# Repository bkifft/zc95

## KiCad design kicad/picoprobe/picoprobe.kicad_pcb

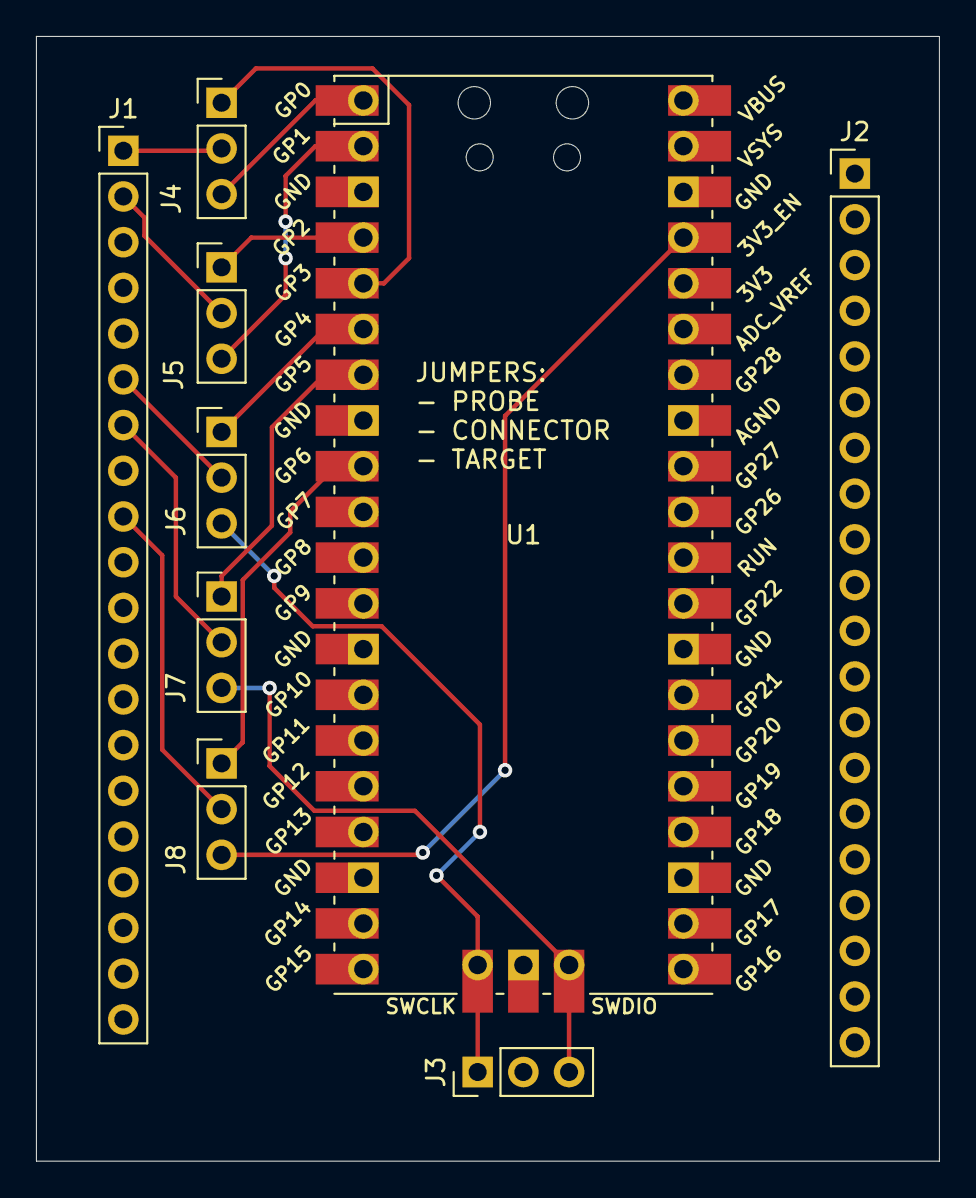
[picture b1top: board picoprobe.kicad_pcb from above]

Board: 2 copper layers, 50.2 x 62.5 mm, 9 parts (0 on the bottom side), 16 nets.

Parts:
J1: Connector left; PinHeader_1x20_P2.54mm_Vertical
J2: Connector right; PinHeader_1x20_P2.54mm_Vertical
J3: SWD; PinHeader_1x03_P2.54mm_Vertical
J4: UART 1; PinHeader_1x03_P2.54mm_Vertical
J5: UART 2; PinHeader_1x03_P2.54mm_Vertical
J6: SWCLK; PinHeader_1x03_P2.54mm_Vertical
J7: SWDIO; PinHeader_1x03_P2.54mm_Vertical
J8: RST; PinHeader_1x03_P2.54mm_Vertical
U1: Pico; RPi_Pico_SMD_TH

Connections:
GND: J1.3, J1.8, J1.13, J1.18, J2.3, J2.8, J2.13, J2.18, J3.2, U1.3, U1.8, U1.13, U1.18, U1.23, U1.28, U1.33, U1.38, U1.42
RST: J1.9, J8.2
SWCLK: J1.6, J6.2
SWDIO: J1.7, J7.2
UART1: J1.1, J4.2
UART2: J1.2, J5.2
pro_rst: J8.1, U1.9
pro_rx: J5.1, U1.4
pro_swclk: J6.1, U1.6
pro_swdio: J7.1, U1.7
pro_tx: J4.1, U1.5
tar_rst: J8.3, U1.37
tar_rx: J4.3, U1.1
tar_swclk: J3.1, J6.3, U1.41
tar_swdio: J3.3, J7.3, U1.43
tar_tx: J5.3, U1.2

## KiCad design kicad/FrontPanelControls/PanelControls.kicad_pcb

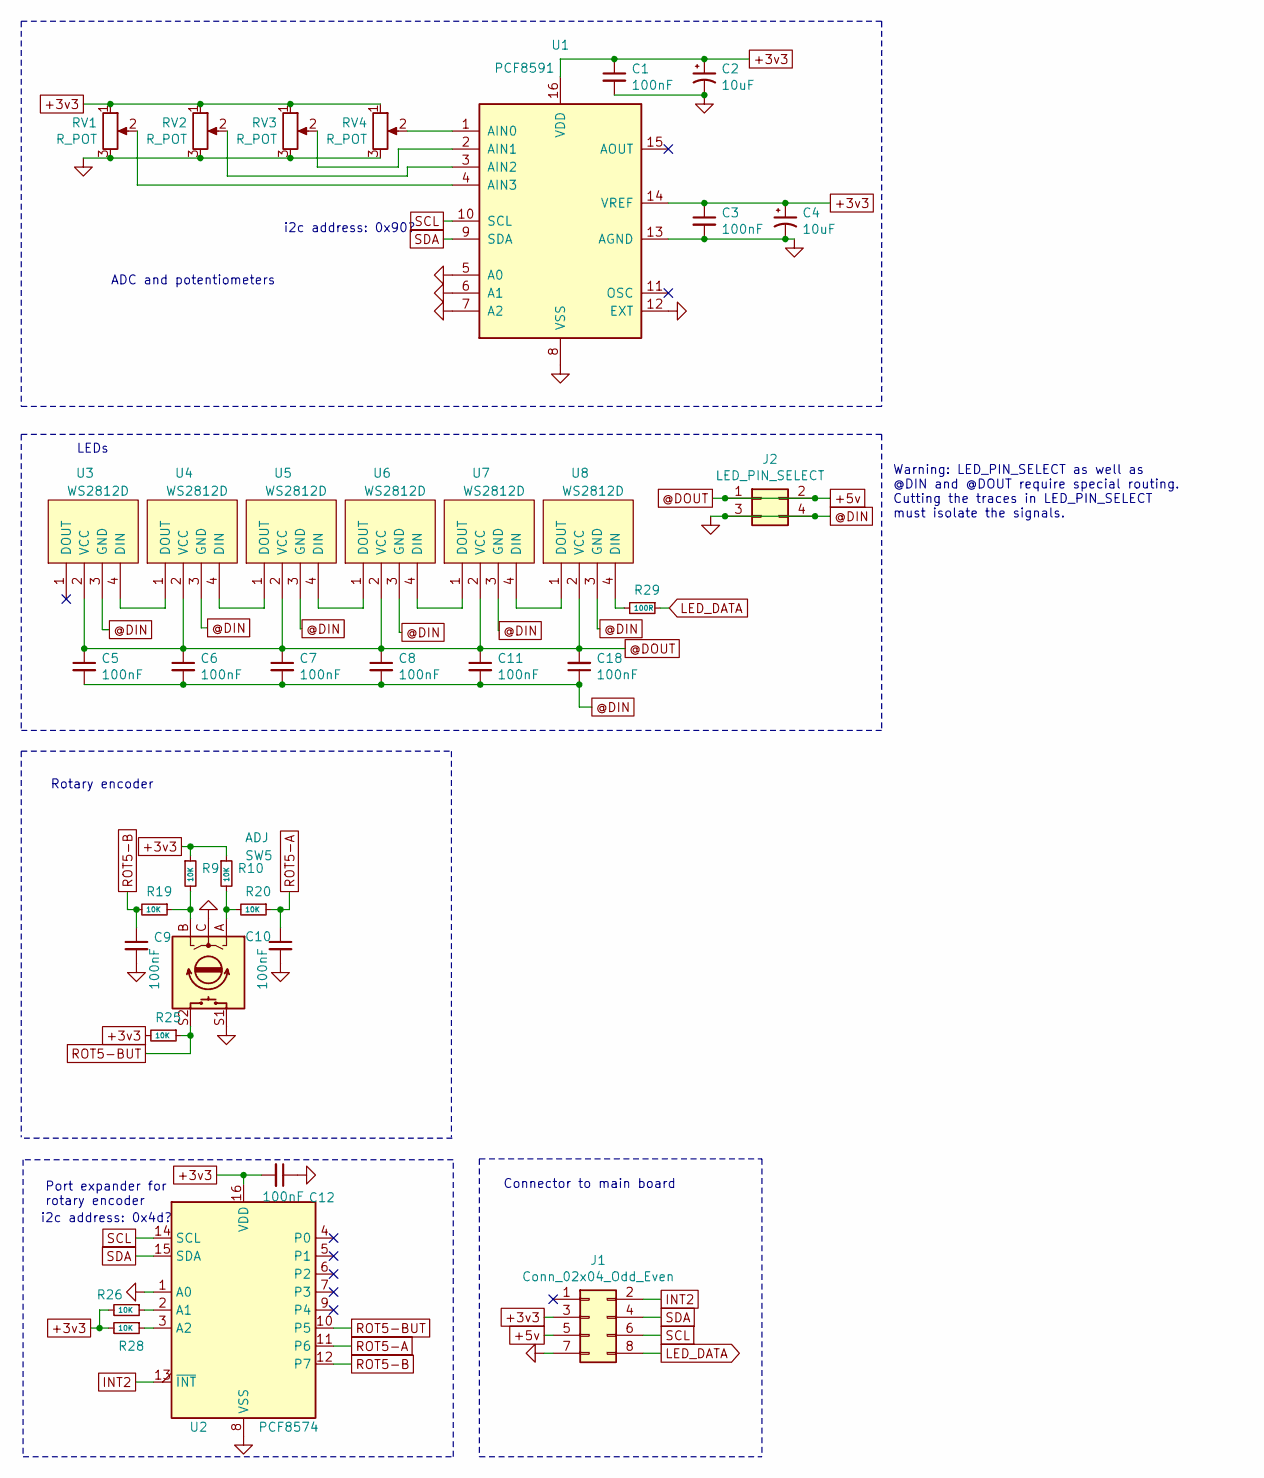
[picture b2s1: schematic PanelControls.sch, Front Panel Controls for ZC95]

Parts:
C1, C3, C5, C6, C7, C8, C9, C10, C11, C12, C18: 100nF; C_Disc_D3.0mm_W2.0mm_P2.50mm
C2, C4: 10uF; CP_Radial_D4.0mm_P2.00mm; LCSC C191532
J1: Conn_02x04_Odd_Even; IDC-Header_2x04_P2.54mm_Vertical
J2: LED_PIN_SELECT; PinHeader_2x02_P2.54mm_Vertical
R9, R10, R19, R20, R25, R26, R28: 10K; R_Axial_DIN0207_L6.3mm_D2.5mm_P7.62mm_Horizontal
R29: 100R; R_Axial_DIN0207_L6.3mm_D2.5mm_P7.62mm_Horizontal
RV1, RV2, RV3, RV4: R_POT; ALPSALPINE RK09L1140A2U
SW5: ADJ; BOURNS PEC11L-4125F-S0020
U1: PCF8591; SO-16_5.3x10.2mm_P1.27mm
U2: PCF8574; DIP-16_W7.62mm_LongPads
U3, U4, U5, U6, U7, U8: WS2812D; WS2812D-F5

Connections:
+3v3: C1.1, C2.1, C3.1, C4.1, C12.2, J1.3, R9.1, R10.1, R25.2, R26.2, R28.2, RV1.1, RV2.1, RV3.1, RV4.1, U1.14 (VREF), U1.16 (VDD), U2.16 (VDD)
+5v: C5.1, C6.1, C7.1, C8.1, C11.1, C18.2, J1.5, J2.1, J2.2, U3.2 (VCC), U4.2 (VCC), U5.2 (VCC), U6.2 (VCC), U7.2 (VCC), U8.2 (VCC)
@DIN: C1.2, C2.2, C3.2, C4.2, C5.2, C6.2, C7.2, C8.2, C9.2, C10.2, C11.2, C12.1, C18.1, J1.7, J2.3, J2.4, RV1.3, RV2.3, RV3.3, RV4.3, SW5.C, SW5.S1, U1.5 (A0), U1.6 (A1), U1.7 (A2), U1.8 (VSS), U1.12 (EXT), U1.13 (AGND), U2.1 (A0), U2.8 (VSS), U3.3 (GND), U4.3 (GND), U5.3 (GND), U6.3 (GND), U7.3 (GND), U8.3 (GND)
INT2: J1.2, U2.13 (~INT~)
LED_DATA: J1.8, R29.1
unnamed: R10.2, R20.2, SW5.A
unnamed: R9.2, R19.1, SW5.B
unnamed: R26.1, U2.2 (A1)
unnamed: R28.1, U2.3 (A2)
unnamed: R29.2, U8.4 (DIN)
unnamed: RV1.2, U1.4 (AIN3)
unnamed: RV2.2, U1.3 (AIN2)
unnamed: RV3.2, U1.2 (AIN1)
unnamed: RV4.2, U1.1 (AIN0)
unnamed: U3.4 (DIN), U4.1 (DOUT)
unnamed: U4.4 (DIN), U5.1 (DOUT)
unnamed: U5.4 (DIN), U6.1 (DOUT)
unnamed: U6.4 (DIN), U7.1 (DOUT)
unnamed: U7.4 (DIN), U8.1 (DOUT)
ROT5-A: C10.1, R20.1, U2.11 (P6)
ROT5-B: C9.1, R19.2, U2.12 (P7)
ROT5-BUT: R25.1, SW5.S2, U2.10 (P5)
SCL: J1.6, U1.10 (SCL), U2.14 (SCL)
SDA: J1.4, U1.9 (SDA), U2.15 (SDA)

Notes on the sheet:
LEDs
ADC and potentiometers
Port expander for rotary encoder
Rotary encoder
Connector to main board
i2c address: 0x90?
i2c address: 0x4d?
Warning: LED_PIN_SELECT as well as @DIN and @DOUT require special routing. Cutting the traces in LED_PIN_SELECT must isolate the signals.

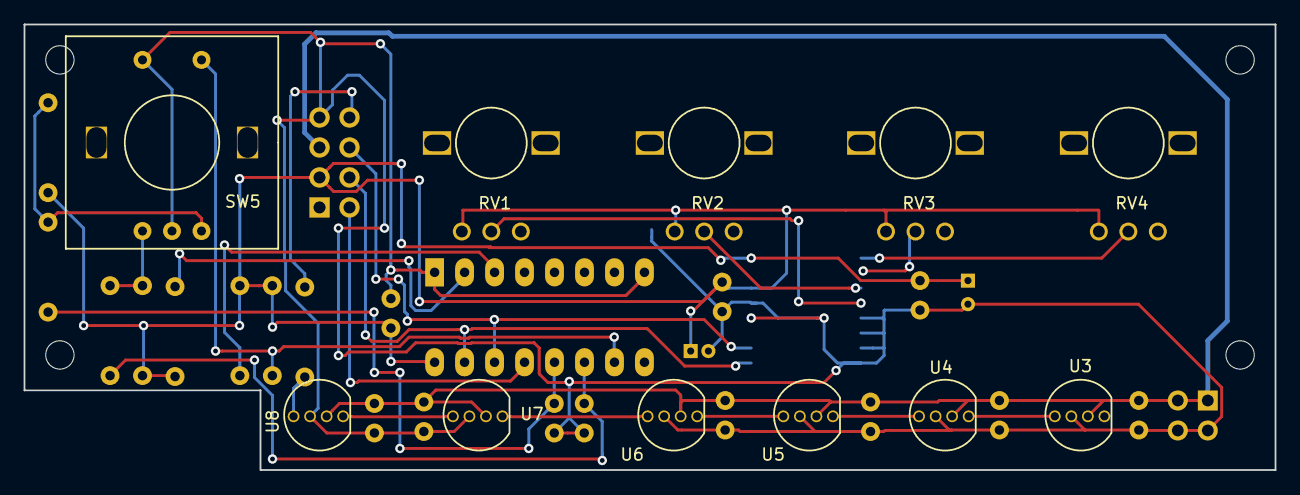
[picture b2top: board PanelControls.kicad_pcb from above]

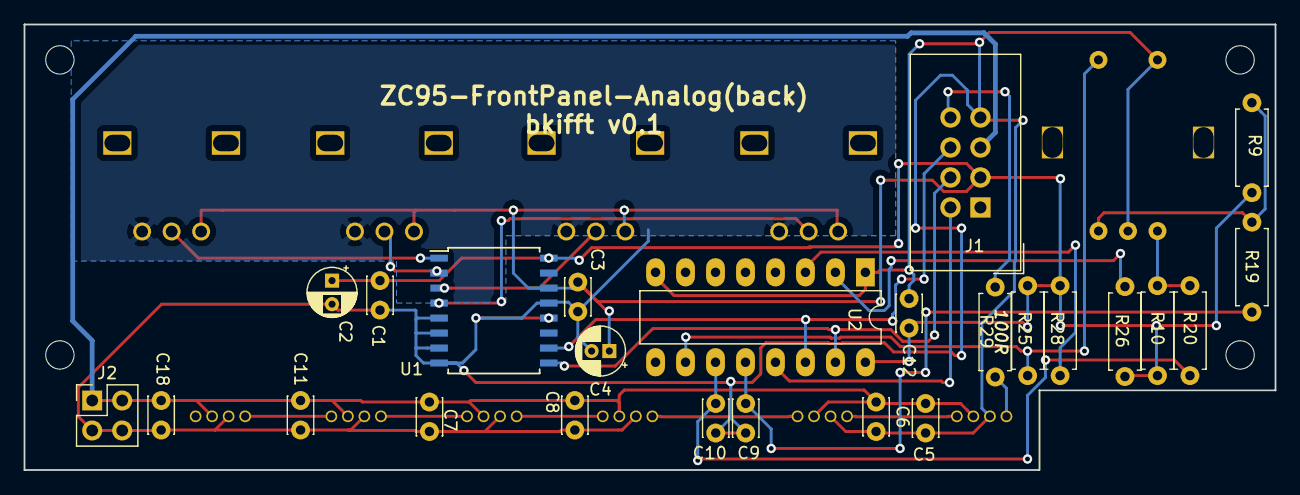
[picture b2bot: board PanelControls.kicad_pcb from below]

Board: 2 copper layers, 106.0 x 37.8 mm, 36 parts (25 on the bottom side), 24 nets.

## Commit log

2022-05-15 CMake changes. builds now also in other directories, added build/ to gitignore, shows progress on auto sdk download
2022-05-22 CMake changes for main
2022-05-22 CMake includes. builds from shell now
2022-05-22 initial notes
2022-06-04 initial changes FrontPanel
2022-06-04 initial version
